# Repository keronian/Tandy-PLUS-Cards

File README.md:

Tandy-PLUS-Cards
================

Tandy PLUS card designs for use in Tandy 1000 EX/HX

I took the work that Jayseon Lee-Steere did creating the Basic and Dual Serial cards as well as the Tandy PLUS Template and used those to create Tandy versions of the Basic and Dual Serial cards.  Additionally, I inverted his ISA to Tandy Plus adapter in order to be able to plug ISA cards into Tandy PLUS slots.  Tandy PLUS Template, EX-HX Combo, and Tandy 1000 Essentials are retained unchanged, but ISA Specific cards were removed to maintain focus for this repo.

Tandy PLUS Template
===================

**Status:** Used to create Dual Serial board

**Description:** A template from which to design cards and/or back plates
for the Tandy 1000 EX/HX computers. Includes approximate board outlines
as measured from Tandy's memory/DMA board, Tandy's serial board and
Rob Krinecki's 3 in 1 board. Includes various notes about safe areas,
potential places to extend the board dimensions, etc.

BasicSerialPlus
===============

**Status:** Untested

**Description:** Adds a single 9 pin serial port to a Tandy 1000 EX/HX. Created with early
Tandy 1000's in mind which have no COM ports from the factory.

Decoding is handled by a 74xx688. Alternatively, a JED file is provided
for programming the needed decode functionality into a GAL16V8/ATF16V8.

**Configuration:** Before installing, configure the port selection jumpers
to a COM port not yet present in the system. Details are located on the
board by the port jumpers. Configure the IRQ jumper to an approriate
selection. For no IRQ, remove the IRQ jumper. Suggested IRQ settings are
located on the board by the IRQ jumper.

DualSerialPlus <sup>1</sup>
==============

**Status:** Tested, works great!

**Description:** Adds *two* 9 pin serial ports to a Tandy 1000 EX/HX. Created with early
Tandy 1000's in mind which have no COM ports from the factory.

**Configuration:** Before installing, configure the port selection jumpers
to COM ports not yet present in the system. Details are located on the
board by the port jumpers. Configure the IRQ jumpers to an approriate
selection. For no IRQ, remove the IRQ jumper. Suggested IRQ settings are
located on the board by the IRQ jumpers.

**Note:** The compact nature of the board means that there are some components on the board
near the back of the machine... This may interfere with ports on other Tandy cards, though
it wouldn't be an issue if you have this card in the top position

DualSerialPlusBracket
=====================

**Status:** Tested, but some small modifications were made after seeing how things lined up,
So the new version should be a better fit, but I can't say with certainty

**Description:** Bracket for the above serial card.  Contains mounting holes for multiple
positions.  There are also User Drawings at various positions that can be used to
change the dimensions if a bracket is desired for a specific position

I have also added .step files that are likely a better option... You can get these CNCed out
of sheet metal for pretty cheap... (1.5mm conductive anodized aluminum seems like the best option I can see)
I also shrank the holes on these .step files to allow for tapping for M3 screws, and added a curved edge
for aesthetic / structural support

EX-HX Combo <sup>1, 2</sup>
===========

**Status:** Presented unchanged from parent repo for reference.

**Description:** Multiple upgrades for the Tandy 1000 EX/HX
in a single board. It adds the following:
* Up to 384K of additional base memory to bring the EX/HX up
  to 640K
* Up to 160K of upper memory (UMB)
* Rear accessable CF card slot
* XT-IDE BIOS
* Serial port with 16550 UART 
* DS1316 SmartWatch real time clock

Functionality is very similar to Rob Krinecki's 3 in 1/4 in 1 boards,
with the following differences:
* Can be fitted in either the lower or middle board position on the
  EX/HX.
* Can be used together with Tandy's original DMA/memory board. This
  configuration adds DMA functionality and makes the top board 
  position available for a third upgrade board.
* Support for additional upper memory on the Tandy 1000 EX. The EX
  allows for more upper memory than the HX due to the EX having a
  smaller system ROM than the HX. 
* Base and upper memory configuration, COM port selection, COM IRQ,
  ATA (IDE) port address, etc. are configurable via dip switches.
  Using the default settings, the board is equivalent to the proven
  configuration of Rob Krineki's 3 in 1 board.

TandyPlusToISA
==============

**Status:** Tested prototype, works perfectly.  Modified so the bracket is a little closer to the back of the case.
Suggest using thicker copper due to the width of the traces, I used 2oz

**Description:** Allows connection of an ISA card to a Tandy 1000 EX/HX Plus slot.

TandyPlusToISA-Long
===================

**Status:** Untested, but is a copy of the above so I don't expect any issues, also suggest 2oz copper weight

**Description:** Same as the above version, but it's a bit longer in cases that the extra clearance is preferred for things like serial ports

---------------
<sup>**1**</sup> Construction requires programming of one or
    more GAL16V8/ATF16V8 and/or GAL22V10/ATF22V10 simple programmable
    logic devices. JED file provided. A TL866 or similar programmer
    can program most of these devices.
    
<sup>**2**</sup> Construction requires programming of the required
    BIOS image into the flash ROM. Most common programmers, such as
    the TL866, can be used for this.

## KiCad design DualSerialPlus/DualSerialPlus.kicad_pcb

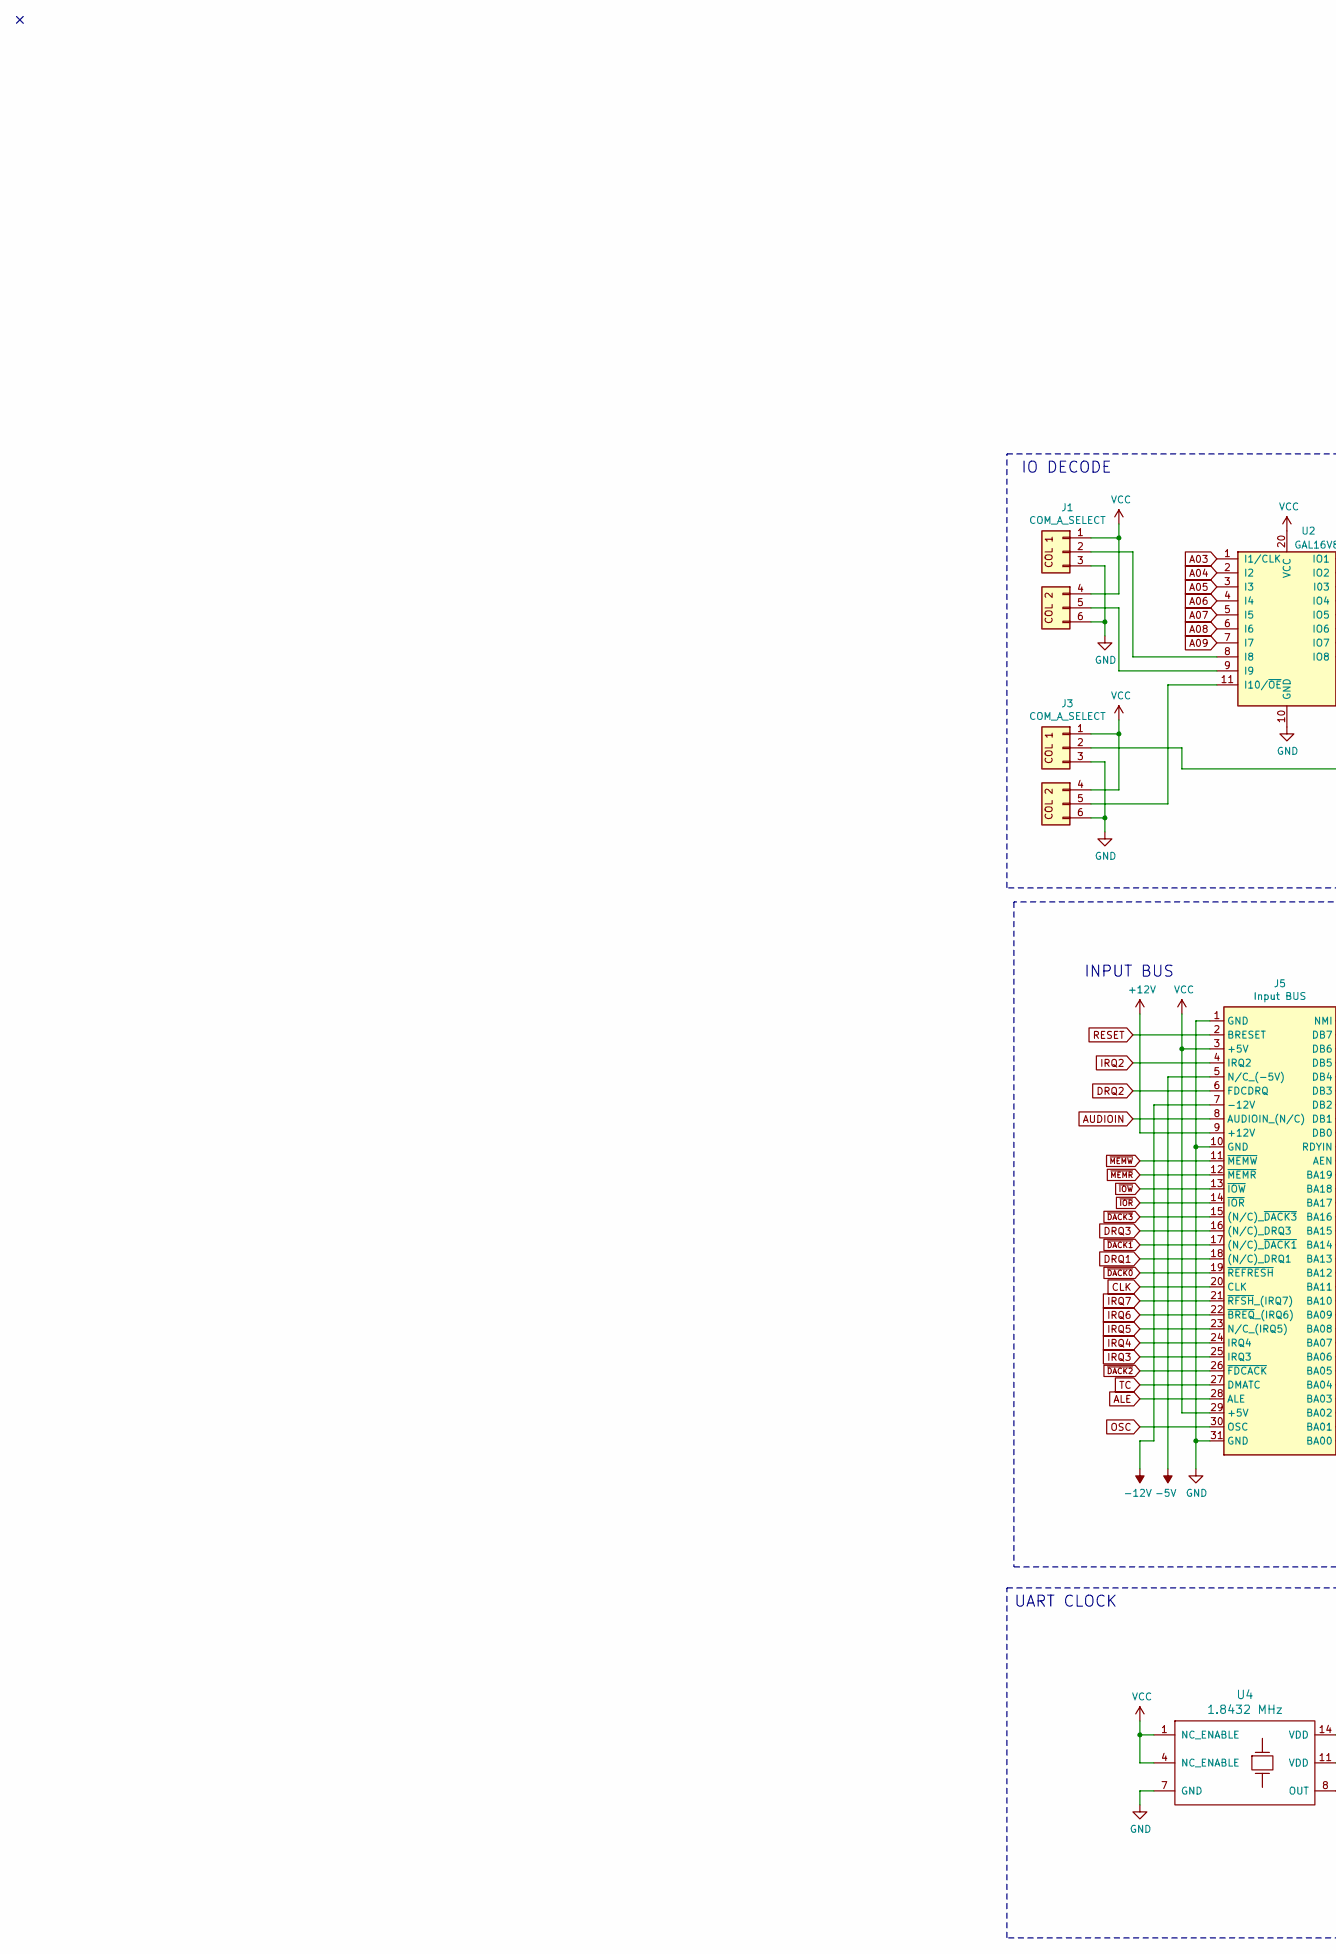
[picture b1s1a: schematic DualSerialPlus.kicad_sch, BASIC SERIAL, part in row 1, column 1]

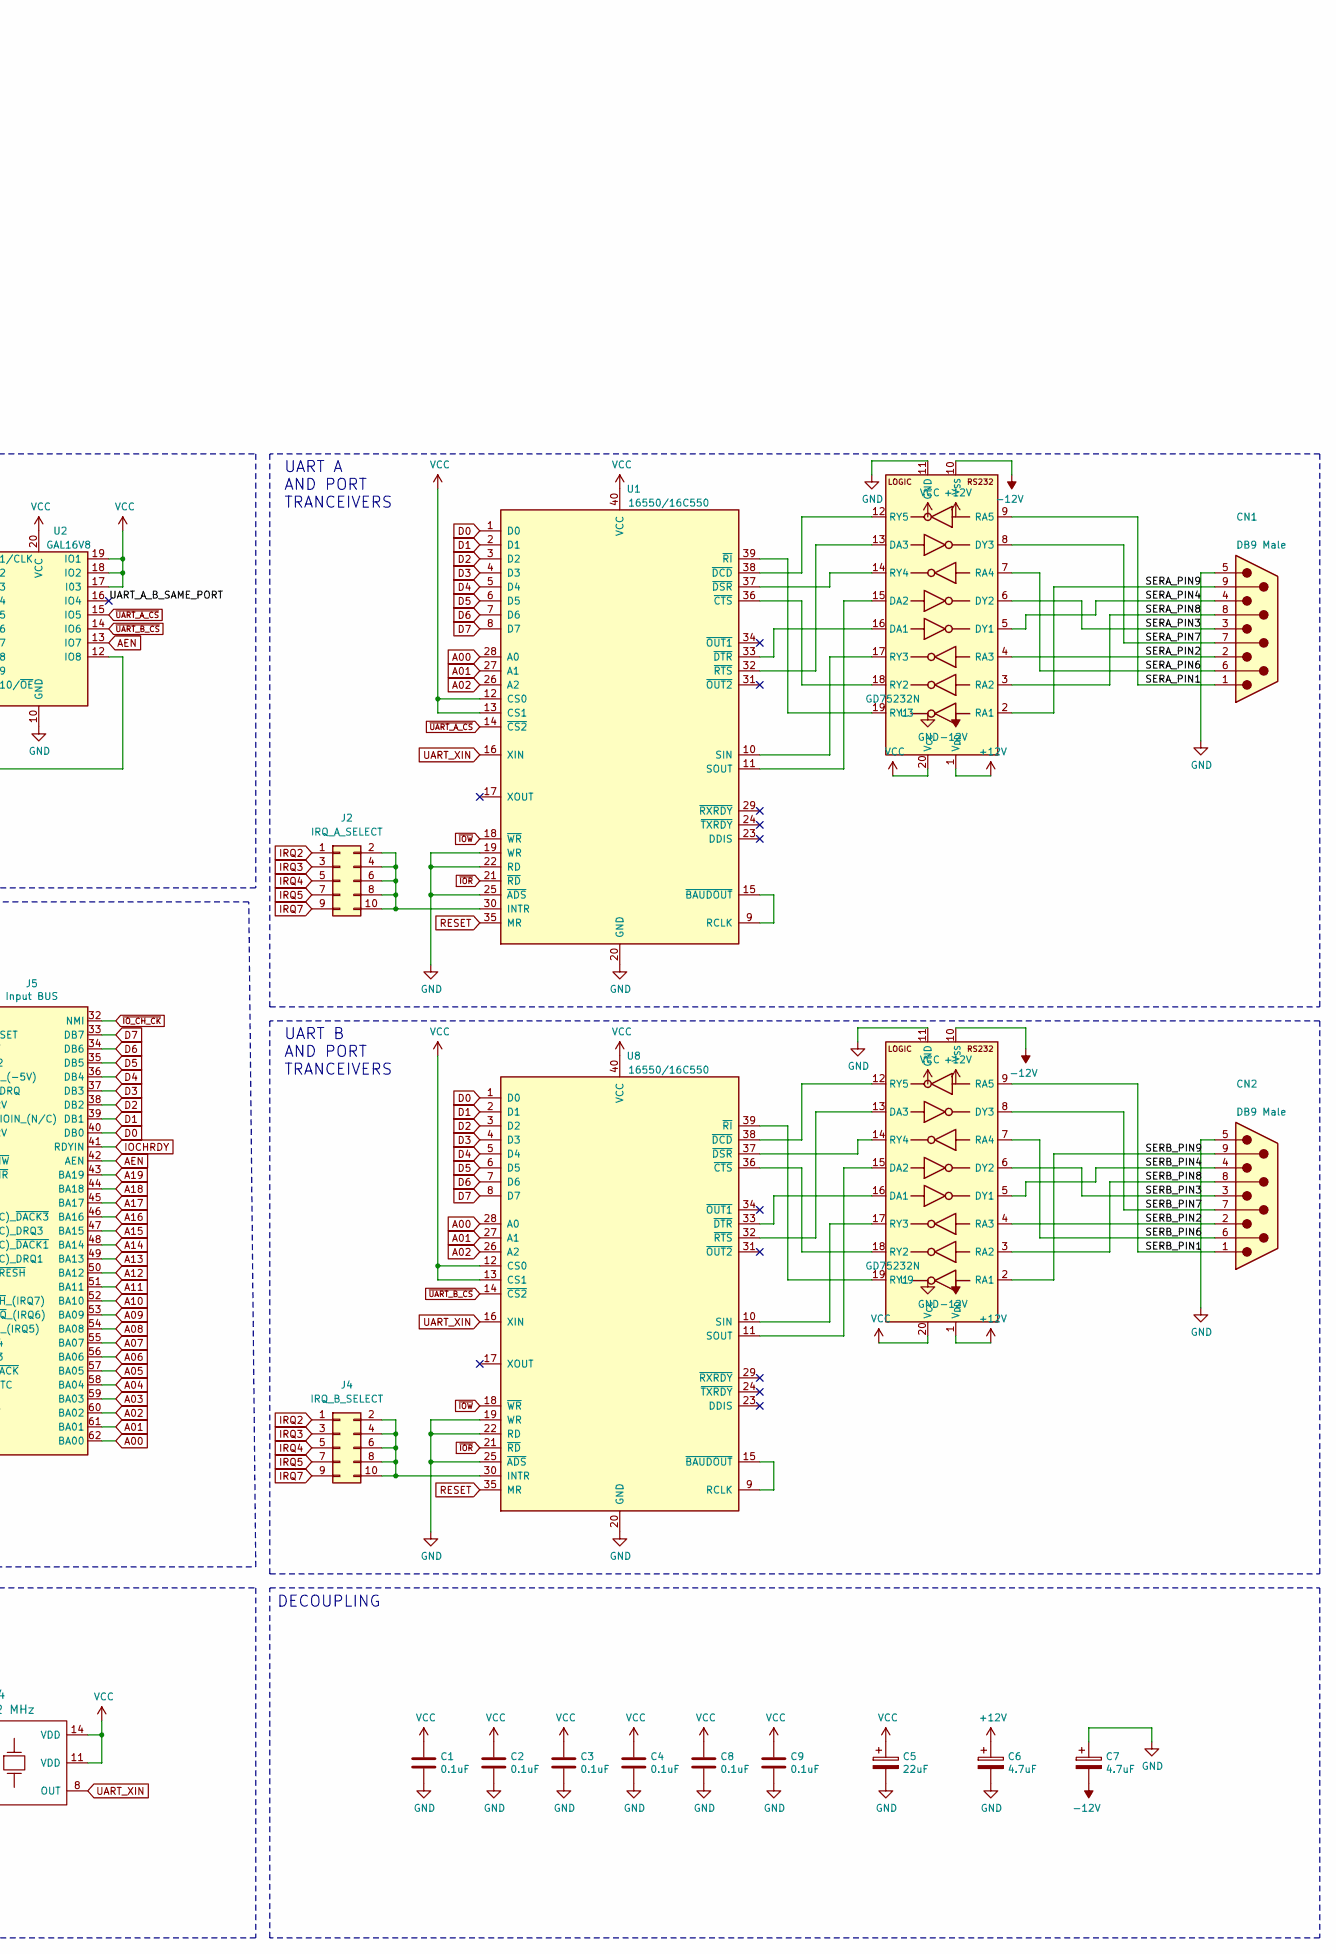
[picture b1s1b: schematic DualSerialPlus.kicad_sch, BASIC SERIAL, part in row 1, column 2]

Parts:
C1, C2, C3, C4, C8, C9: 0.1uF; C_Disc_D5.1mm_W3.2mm_P5.00mm
C5: 22uF; CP_Radial_D7.5mm_P2.50mm
C6, C7: 4.7uF; CP_Radial_D7.5mm_P2.50mm
CN1, CN2: DB9 Male; DB_9M
J1, J3: COM_A_SELECT; PinHeader_3x02_P2.54mm_Vertical
J2: IRQ_A_SELECT; PinHeader_2x05_P2.54mm_Vertical
J4: IRQ_B_SELECT; PinHeader_2x05_P2.54mm_Vertical
J5: Input BUS; TandyPlusSocket
U1, U8: 16550/16C550; DIP-40_W15.24mm_Socket
U2: GAL16V8; DIP-20_W7.62mm_Socket
U3, U9: GD75232N; DIP-20_W7.62mm_Socket
U4: 1.8432 MHz; Crystal_DIP8_DIP14

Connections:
+12V: C6.1, J5.9 (+12V), U3.1 (V_{DD}), U9.1 (V_{DD})
-5V: J5.5 (N/C_(-5V))
-12V: C7.2, J5.7 (-12V), U3.10 (V_{SS}), U9.10 (V_{SS})
/SERA_PIN1: CN1.1, U3.9 (RA5)
/SERA_PIN2: CN1.2, U3.4 (RA3)
/SERA_PIN3: CN1.3, U3.6 (DY2)
/SERA_PIN4: CN1.4, U3.5 (DY1)
/SERA_PIN6: CN1.6, U3.7 (RA4)
/SERA_PIN7: CN1.7, U3.8 (DY3)
/SERA_PIN8: CN1.8, U3.3 (RA2)
/SERA_PIN9: CN1.9, U3.2 (RA1)
/SERB_PIN1: CN2.1, U9.9 (RA5)
/SERB_PIN2: CN2.2, U9.4 (RA3)
/SERB_PIN3: CN2.3, U9.6 (DY2)
/SERB_PIN4: CN2.4, U9.5 (DY1)
/SERB_PIN6: CN2.6, U9.7 (RA4)
/SERB_PIN7: CN2.7, U9.8 (DY3)
/SERB_PIN8: CN2.8, U9.3 (RA2)
/SERB_PIN9: CN2.9, U9.2 (RA1)
/UART_A_B_SAME_PORT: U2.16 (IO4)
A00: J5.62 (BA00), U1.28 (A0), U8.28 (A0)
A01: J5.61 (BA01), U1.27 (A1), U8.27 (A1)
A02: J5.60 (BA02), U1.26 (A2), U8.26 (A2)
A03: J5.59 (BA03), U2.1 (I1/CLK)
A04: J5.58 (BA04), U2.2 (I2)
A05: J5.57 (BA05), U2.3 (I3)
A06: J5.56 (BA06), U2.4 (I4)
A07: J5.55 (BA07), U2.5 (I5)
A08: J5.54 (BA08), U2.6 (I6)
A09: J5.53 (BA09), U2.7 (I7)
A10: J5.52 (BA10)
A11: J5.51 (BA11)
A12: J5.50 (BA12)
A13: J5.49 (BA13)
A14: J5.48 (BA14)
A15: J5.47 (BA15)
A16: J5.46 (BA16)
A17: J5.45 (BA17)
A18: J5.44 (BA18)
A19: J5.43 (BA19)
AEN: J5.42 (AEN), U2.13 (IO7)
ALE: J5.28 (ALE)
AUDIOIN: J5.8 (AUDIOIN_(N/C))
CLK: J5.20 (CLK)
D0: J5.40 (DB0), U1.1 (D0), U8.1 (D0)
D1: J5.39 (DB1), U1.2 (D1), U8.2 (D1)
D2: J5.38 (DB2), U1.3 (D2), U8.3 (D2)
D3: J5.37 (DB3), U1.4 (D3), U8.4 (D3)
D4: J5.36 (DB4), U1.5 (D4), U8.5 (D4)
D5: J5.35 (DB5), U1.6 (D5), U8.6 (D5)
D6: J5.34 (DB6), U1.7 (D6), U8.7 (D6)
D7: J5.33 (DB7), U1.8 (D7), U8.8 (D7)
DRQ1: J5.18 ((N/C)_DRQ1)
DRQ2: J5.6 (FDCDRQ)
DRQ3: J5.16 ((N/C)_DRQ3)
GND: C1.2, C2.2, C3.2, C4.2, C5.2, C6.2, C7.1, C8.2, C9.2, CN1.5, CN2.5, J1.3 (Pin_4), J1.6, J3.3 (Pin_4), J3.6, J5.1 (GND), J5.10 (GND), J5.31 (GND), U1.19 (WR), U1.20 (GND), U1.22 (RD), U1.25 (~ADS), U2.10 (GND), U3.11 (GND), U4.7 (GND), U8.19 (WR), U8.20 (GND), U8.22 (RD), U8.25 (~ADS), U9.11 (GND)
IOCHRDY: J5.41 (RDYIN)
IRQ2: J2.1, J4.1, J5.4 (IRQ2)
IRQ3: J2.3, J4.3, J5.25 (IRQ3)
IRQ4: J2.5, J4.5, J5.24 (IRQ4)
IRQ5: J2.7, J4.7, J5.23 (N/C_(IRQ5))
IRQ6: J5.22 (~BREQ_(IRQ6))
IRQ7: J2.9, J4.9, J5.21 (~RFSH_(IRQ7))
unnamed: J1.2, U2.8 (I8)
unnamed: J1.5, U2.9 (I9)
unnamed: J2.2, J2.4, J2.6, J2.8, J2.10, U1.30 (INTR)
unnamed: J3.2, U2.12 (IO8)
unnamed: J3.5, U2.11 (I10/~OE)
unnamed: J4.2, J4.4, J4.6, J4.8, J4.10, U8.30 (INTR)
unnamed: U1.9 (RCLK), U1.15 (~BAUDOUT)
unnamed: U1.10 (SIN), U3.17 (RY3)
unnamed: U1.11 (SOUT), U3.15 (DA2)
unnamed: U1.36 (~CTS), U3.18 (RY2)
unnamed: U1.38 (~DCD), U3.12 (RY5)
unnamed: U1.37 (~DSR), U3.14 (RY4)
unnamed: U1.33 (~DTR), U3.16 (DA1)
unnamed: U1.39 (~RI), U3.19 (RY1)
unnamed: U1.32 (~RTS), U3.13 (DA3)
unnamed: U8.9 (RCLK), U8.15 (~BAUDOUT)
unnamed: U8.10 (SIN), U9.17 (RY3)
unnamed: U8.11 (SOUT), U9.15 (DA2)
unnamed: U8.36 (~CTS), U9.18 (RY2)
unnamed: U8.38 (~DCD), U9.12 (RY5)
unnamed: U8.37 (~DSR), U9.14 (RY4)
unnamed: U8.33 (~DTR), U9.16 (DA1)
unnamed: U8.39 (~RI), U9.19 (RY1)
unnamed: U8.32 (~RTS), U9.13 (DA3)
OSC: J5.30 (OSC)
RESET: J5.2 (BRESET), U1.35 (MR), U8.35 (MR)
TC: J5.27 (DMATC)
UART_XIN: U1.16 (XIN), U4.8 (OUT), U8.16 (XIN)
VCC: C1.1, C2.1, C3.1, C4.1, C5.1, C8.1, C9.1, J1.1, J1.4, J3.1, J3.4, J5.3 (+5V), J5.29 (+5V), U1.12 (CS0), U1.13 (CS1), U1.40 (VCC), U2.17 (I03), U2.18 (IO2), U2.19 (IO1), U2.20 (VCC), U3.20 (V_{CC}), U4.1 (NC_ENABLE), U4.4 (NC_ENABLE), U4.11 (VDD), U4.14 (VDD), U8.12 (CS0), U8.13 (CS1), U8.40 (VCC), U9.20 (V_{CC})
~DACK0: J5.19 (~REFRESH)
~DACK1: J5.17 ((N/C)_~DACK1)
~DACK2: J5.26 (~FDCACK)
~DACK3: J5.15 ((N/C)_~DACK3)
~IOR: J5.14 (~IOR), U1.21 (~RD), U8.21 (~RD)
~IOW: J5.13 (~IOW), U1.18 (~WR), U8.18 (~WR)
~IO_CH_CK: J5.32 (NMI)
~MEMR: J5.12 (~MEMR)
~MEMW: J5.11 (~MEMW)
~UART_A_CS: U1.14 (~CS2), U2.15 (IO5)
~UART_B_CS: U2.14 (IO6), U8.14 (~CS2)

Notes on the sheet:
INPUT BUS
UART B AND PORT TRANCEIVERS
DECOUPLING
UART CLOCK
UART A AND PORT TRANCEIVERS
IO DECODE

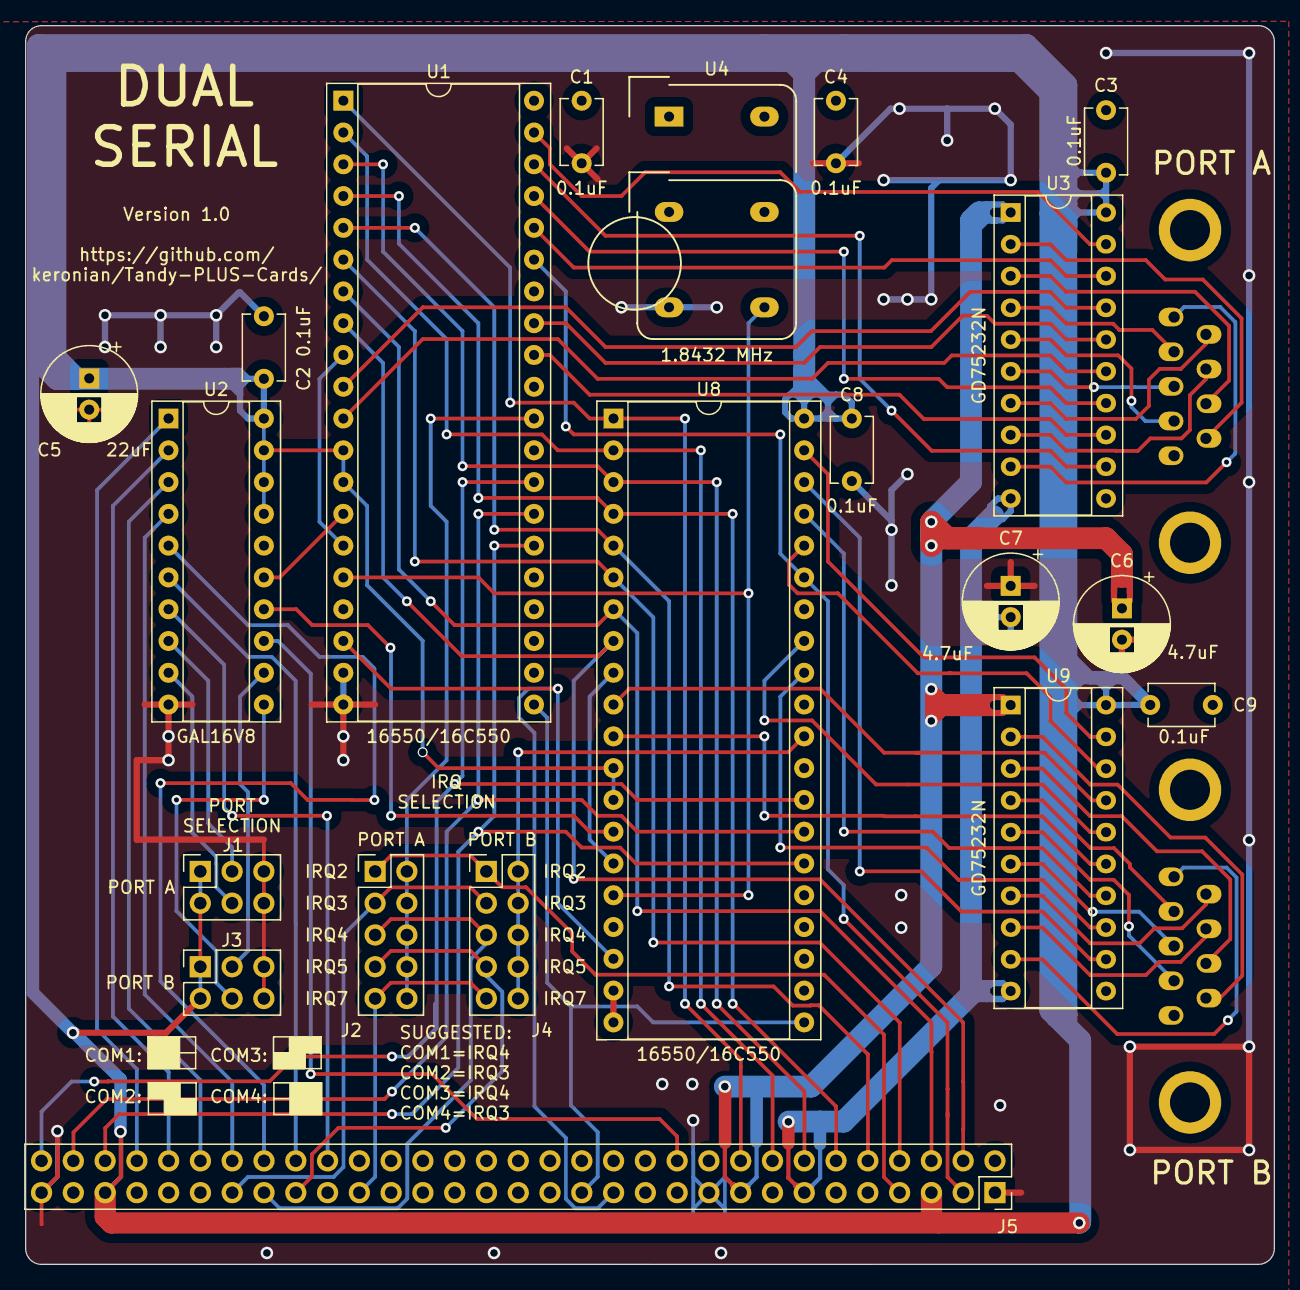
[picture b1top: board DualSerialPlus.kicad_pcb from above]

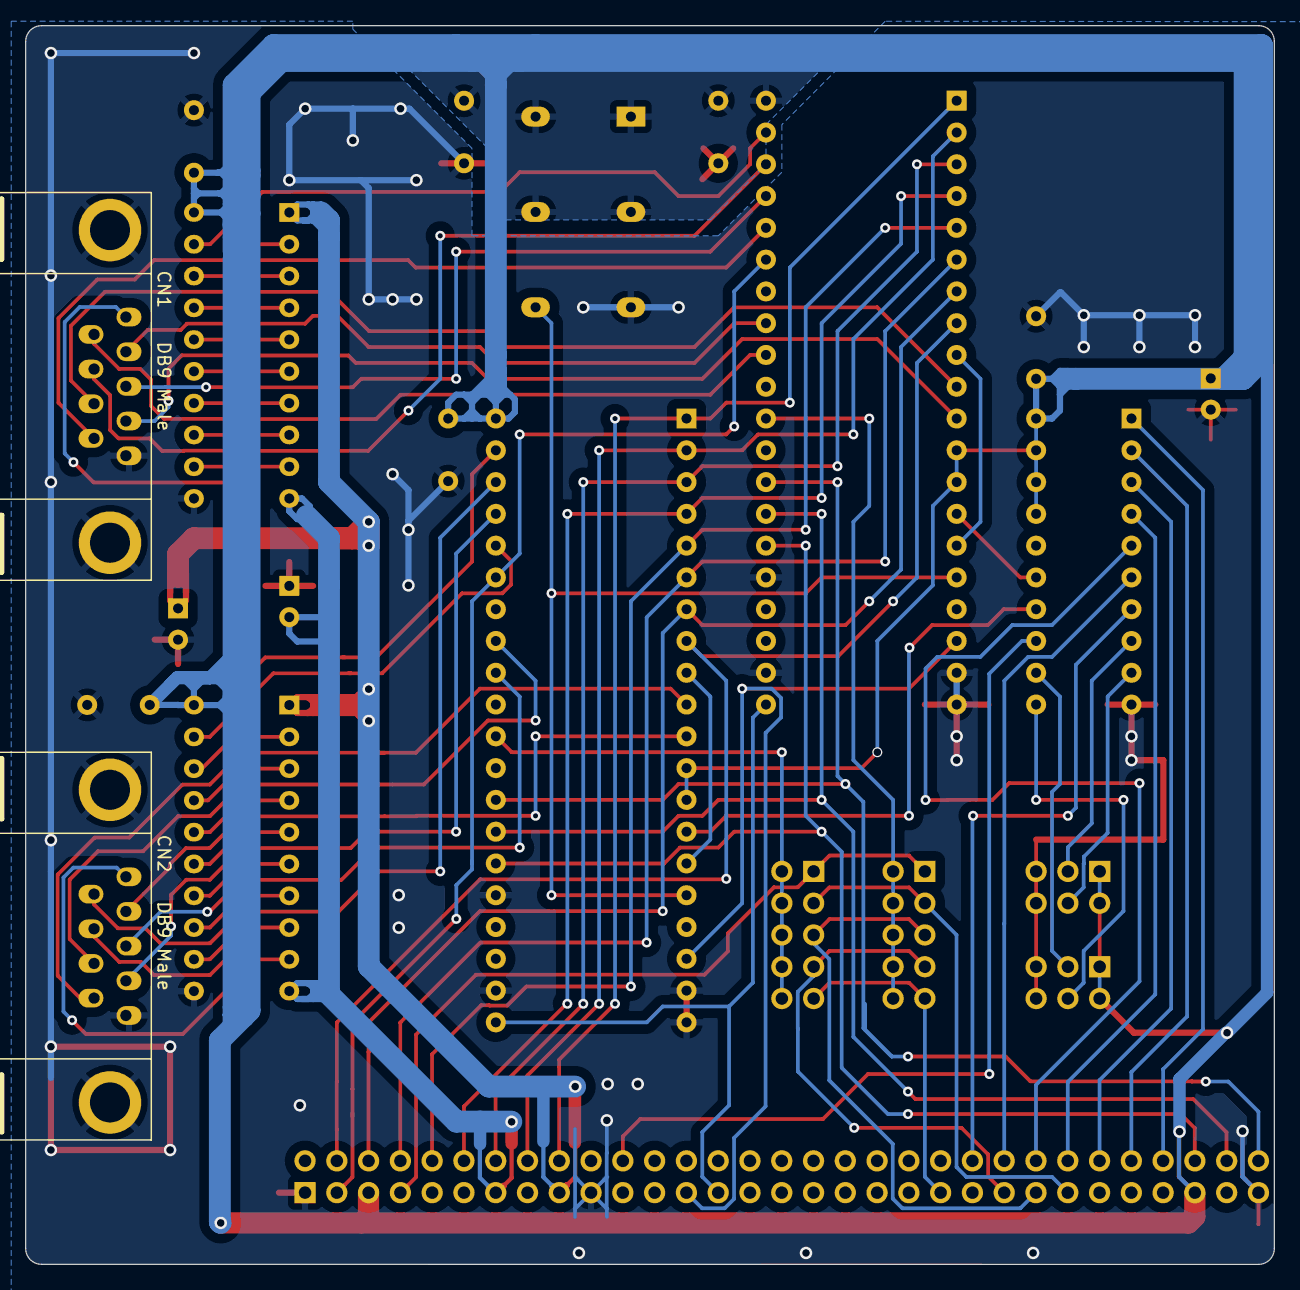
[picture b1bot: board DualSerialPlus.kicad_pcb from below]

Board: 2 copper layers, 99.8 x 99.0 mm, 22 parts (2 on the bottom side), 74 nets.

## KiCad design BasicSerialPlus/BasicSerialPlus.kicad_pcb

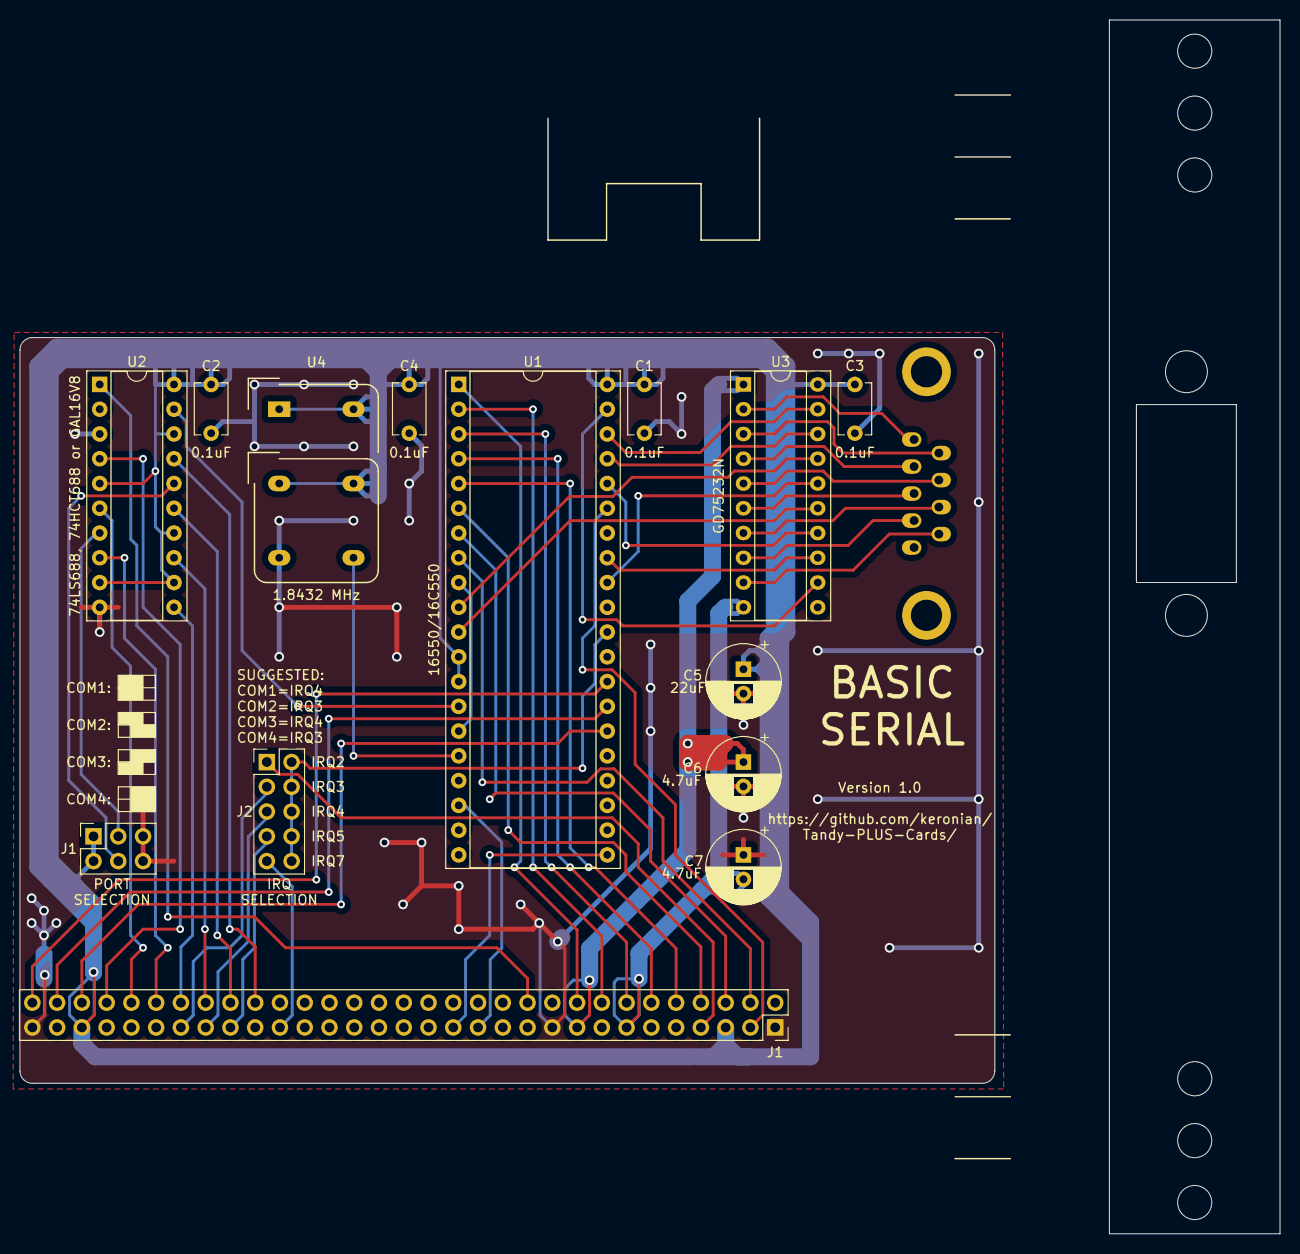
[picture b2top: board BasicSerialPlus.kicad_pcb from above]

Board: 2 copper layers, 100.0 x 76.5 mm, 23 parts (1 on the bottom side), 53 nets.

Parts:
C1, C2, C3, C4: 0.1uF; C_Disc_D5.1mm_W3.2mm_P5.00mm
C5: 22uF; CP_Radial_D7.5mm_P2.50mm
C6, C7: 4.7uF; CP_Radial_D7.5mm_P2.50mm
CN1: DB9 Male; DB_9M
H1, H2, H3, H4, H5, H6: MountingHole_Pad; MountingHole_3.5mm
HA1, HA2: MountingHole_4.3mm_M4_DIN965
J1: COM_SELECT; PinHeader_3x02_P2.54mm_Vertical
J1#2: Input BUS; TandyPlusSocket
J2: IRQ_SELECT; PinHeader_2x05_P2.54mm_Vertical
U1: 16550/16C550; DIP-40_W15.24mm_Socket
U2: 74LS688, 74HCT688 or GAL16V8; DIP-20_W7.62mm_Socket
U3: GD75232N; DIP-20_W7.62mm_Socket
U4: 1.8432 MHz; Crystal_DIP8_DIP14

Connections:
+12V: C6.1, J1#2.9, U3.1
-12V: C7.2, J1#2.7, U3.10
/SER_PIN1: CN1.1, U3.2
/SER_PIN2: CN1.2, U3.4
/SER_PIN3: CN1.3, U3.6
/SER_PIN4: CN1.4, U3.8
/SER_PIN6: CN1.6, U3.3
/SER_PIN7: CN1.7, U3.5
/SER_PIN8: CN1.8, U3.7
/SER_PIN9: CN1.9, U3.9
A00: J1#2.62, U1.28
A01: J1#2.61, U1.27
A02: J1#2.60, U1.26
A03: J1#2.59, U2.4
A04: J1#2.58, U2.6
A05: J1#2.57, U2.8
A06: J1#2.56, U2.11
A07: J1#2.55, U2.13
A08: J1#2.54, U2.15
A09: J1#2.53, U2.17
AEN: J1#2.42, U2.1
D0: J1#2.40, U1.1
D1: J1#2.39, U1.2
D2: J1#2.38, U1.3
D3: J1#2.37, U1.4
D4: J1#2.36, U1.5
D5: J1#2.35, U1.6
D6: J1#2.34, U1.7
D7: J1#2.33, U1.8
GND: C1.2, C2.2, C3.2, C4.2, C5.2, C6.2, C7.1, CN1.5, J1.3, J1.6, J1#2.1, J1#2.10, J1#2.31, U1.19, U1.20, U1.22, U1.25, U2.2, U2.3, U2.10, U3.11, U4.7
IRQ2: J1#2.4, J2.1
IRQ3: J1#2.25, J2.3
IRQ4: J1#2.24, J2.5
IRQ5: J1#2.23, J2.7
IRQ7: J1#2.21, J2.9
unnamed: J1.2, U2.7
unnamed: J1.5, U2.16
unnamed: J2.2, J2.4, J2.6, J2.8, J2.10, U1.30
unnamed: U1.10, U3.17
unnamed: U1.11, U3.15
unnamed: U1.9, U1.15
unnamed: U1.32, U3.16
unnamed: U1.33, U3.13
unnamed: U1.36, U3.14
unnamed: U1.37, U3.18
unnamed: U1.38, U3.19
unnamed: U1.39, U3.12
RESET: J1#2.2, U1.35
UART_XIN: U1.16, U4.8
VCC: C1.1, C2.1, C3.1, C4.1, C5.1, J1.1, J1.4, J1#2.3, J1#2.29, U1.12, U1.13, U1.40, U2.5, U2.9, U2.12, U2.14, U2.18, U2.20, U3.20, U4.1, U4.4, U4.11, U4.14
~IOR: J1#2.14, U1.21
~IOW: J1#2.13, U1.18
~UART_CS: U1.14, U2.19

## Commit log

2026-04-01 Initial commit with Tandy PLUS Dual Serial card and ISA adapter
2026-04-01 Removed Riser from Readme
2026-04-02 Added BasicSerialPlus
2026-04-05 Realized on PLUS cards, the ports need to be on the UNDERSIDE to line up properly
2026-04-07 Shifted Plus to ISA adapters a little, updated tested status
2026-04-09 Updated readme to reflect inclusion of the Basic serial card
2026-04-12 Added image of Tandy PLUS to ISA card
2026-04-12 Fixed typo
2026-04-12 Removing the "Tandy 1000 Essentials" project as it's not for EX/HX PLUS connector
2026-04-17 Updated bracket, added info about working dual serial card
2026-04-18 added images for the dual serial card
2026-04-18 Shifted cutout for basic serial bracket
2026-04-18 added step files for the dualserial bracket so they can be 3d printed
2026-04-18 Modified .step files for M3 tapping
2026-05-07 Updated bracket step files to be more compatible with sheet metal fabrication

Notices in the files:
DualSerialPlus/DualSerialPlus.kicad_sch:
Copyright (C) 2021 Titanium Studios Pty Ltd
